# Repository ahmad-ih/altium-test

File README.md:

View this project on [CADLAB.io](https://cadlab.io/project/22601). 

# ANAVI Infrared pHAT

ANAVI Infrared pHAT is an open source hardware Raspberry Pi pHAT (add-on board) for rapid prototyping of Internet of Things (IoT) powered by free and open source software. It features:

* 2x IR transmitters
* IR receiver (IR photo sensor)
* Slots for up to 3 plug and play I2C sensors for temperature, barometric pressure, humidity and light
* UART (Universal asynchronous receiver/transmitter) pins for debugging

ANAVI Infrared pHAT is available at [CrowdSupply](https://www.crowdsupply.com/anavi-technology/infrared-phat).

# License

The project is released under the [Creative Commons Attribution-ShareAlike 4.0 International (CC BY-SA 4.0)](https://creativecommons.org/licenses/by-sa/4.0/).

Note: This is a human-readable summary of (and not a substitute for) the [license](https://creativecommons.org/licenses/by-sa/4.0/legalcode).

You are free to:

Share — copy and redistribute the material in any medium or format Adapt — remix, transform, and build upon the material for any purpose, even commercially. The licensor cannot revoke these freedoms as long as you follow the license terms. Under the following terms:

Attribution — You must give appropriate credit, provide a link to the license, and indicate if changes were made. You may do so in any reasonable manner, but not in any way that suggests the licensor endorses you or your use. ShareAlike — If you remix, transform, or build upon the material, you must distribute your contributions under the same license as the original. No additional restrictions — You may not apply legal terms or technological measures that legally restrict others from doing anything the license permits. Notices:

You do not have to comply with the license for elements of the material in the public domain or where your use is permitted by an applicable exception or limitation. No warranties are given. The license may not give you all of the permissions necessary for your intended use. For example, other rights such as publicity, privacy, or moral rights may limit how you use the material.

You will have to provide a link to the original creator of the project http://www.anavi.technology on any documentation or website.

Credit can be attributed through a link to the creator website: http://www.anavi.technology

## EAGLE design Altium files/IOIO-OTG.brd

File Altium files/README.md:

## NanoBoard-NB1

The NanoBoard-NB1 is Altium's legacy development platform for the rapid testing of FPGA designs. It consists of a motherboard with a variety of commonly used peripherals, and a range of plug-in FPGA or CPLD daughter boards.

The emergence of low-cost FPGA and CPLD devices from multiple vendors has resulted in the need
for a state of the art development system. The NB1 NanoBoard, in conjunction with the Altium
Designer PC-based development software allows hardware engineers and embedded systems
developers to develop and evaluate complex programmable logic-based systems.

In addition to providing schematic and PCB tools, the Altium Designer development system also allows
complete FPGA designs to be created, designed and debugged. FPGA projects can be created with
the schematic editor, using supplied schematic library components covering an extensive palette of IP
functions, including a range of industry-standard microcontrollers. 

The NanoBoard includes a unique communications protocol called NanoTalk, that provides connection
between a host PC running the software and the NanoBoard. NanoTalk provides the ability to
daisychain a number of NanoBoards, and communications access from the software to all resources
on the NanoBoard, or daisychained sequence of NanoBoards. 

Documentation
--------------
* **[Technical Reference for Altium's NanoBoard-NB1](http://valhalla.altium.com/Learning-Guides/Legacy/TR0102%20NanoBoard%20Technical%20Reference%20Manual%20-%20NB1.pdf)**
* **[Bootstrapping the Daughter Board FPGA on the NanoBoard-NB1](https://techdocs.altium.com/display/ADOH/Bootstrapping+the+Daughter+Board+FPGA+on+the+NanoBoard-NB1)**
* **[Utilizing the SPI Flash Memory on the NanoBoard-NB1](https://techdocs.altium.com/display/ADOH/Utilizing+the+SPI+Flash+Memory+on+the+NanoBoard-NB1)**
* **[Updating the Firmware on the NanoBoard-NB1](https://techdocs.altium.com/display/ADOH/Updating+the+Firmware+on+the+NanoBoard-NB1)**

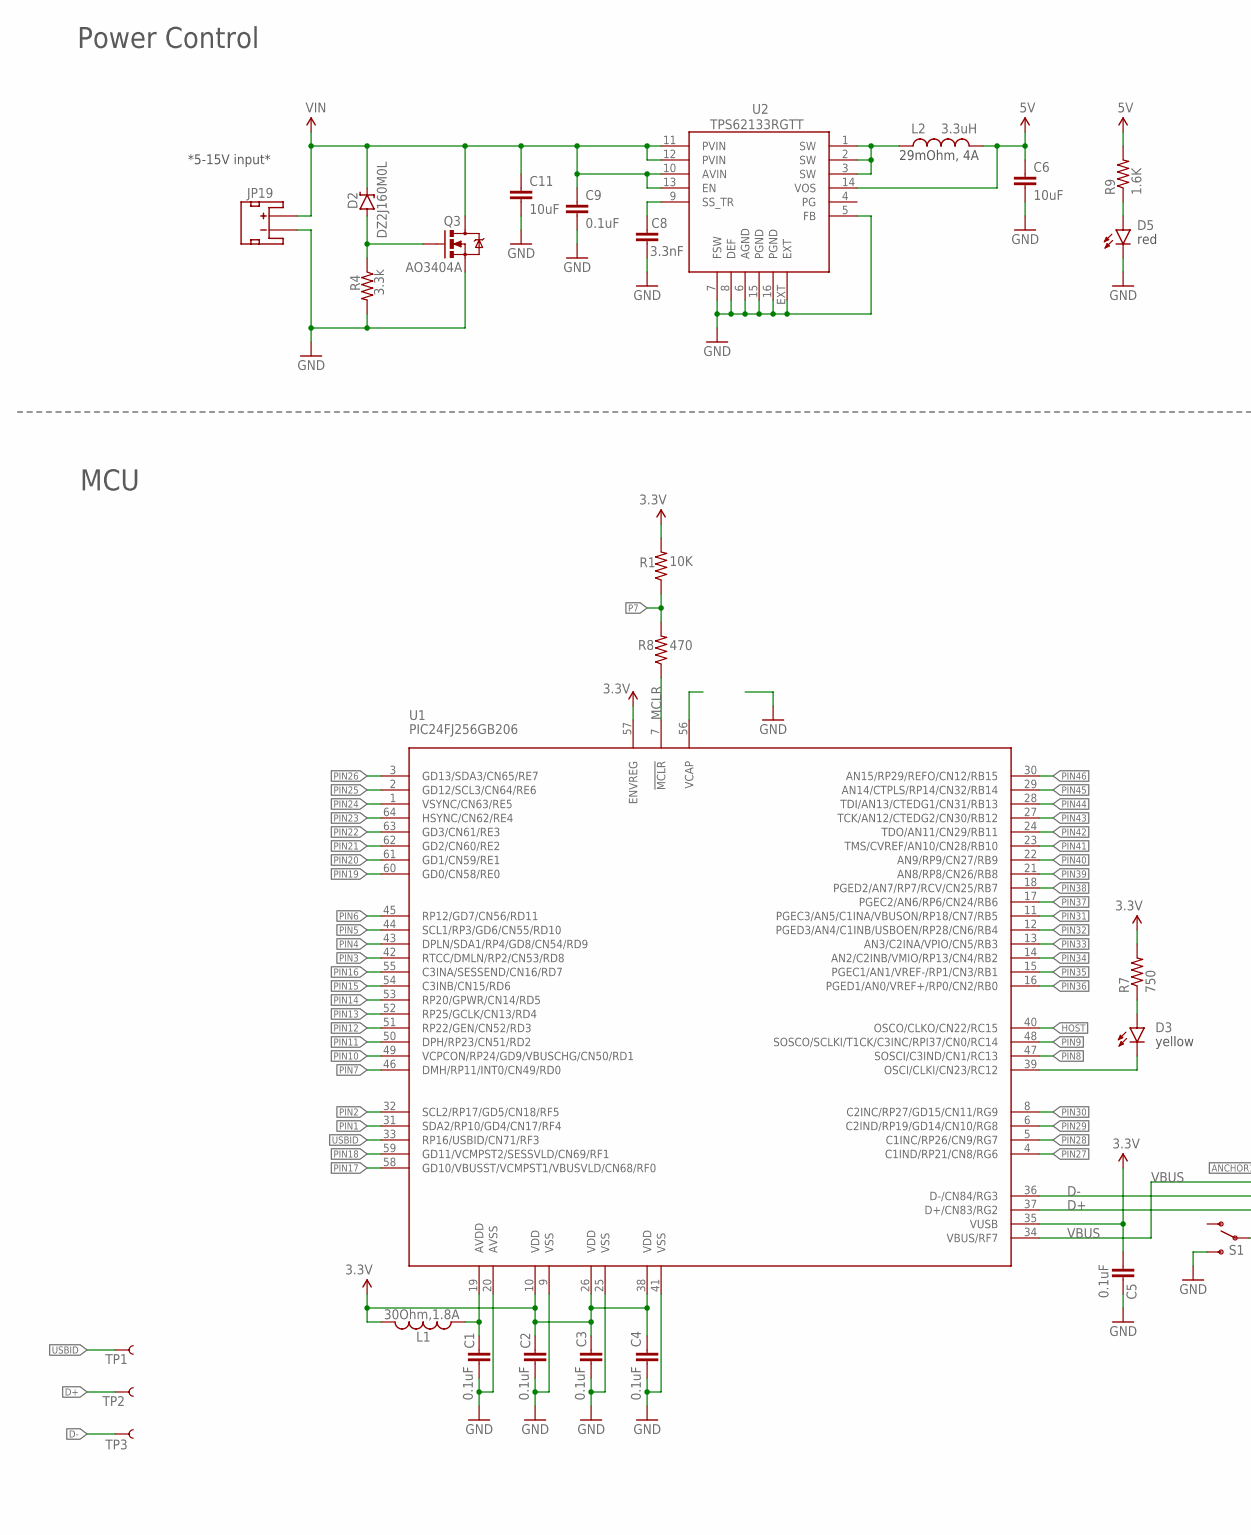
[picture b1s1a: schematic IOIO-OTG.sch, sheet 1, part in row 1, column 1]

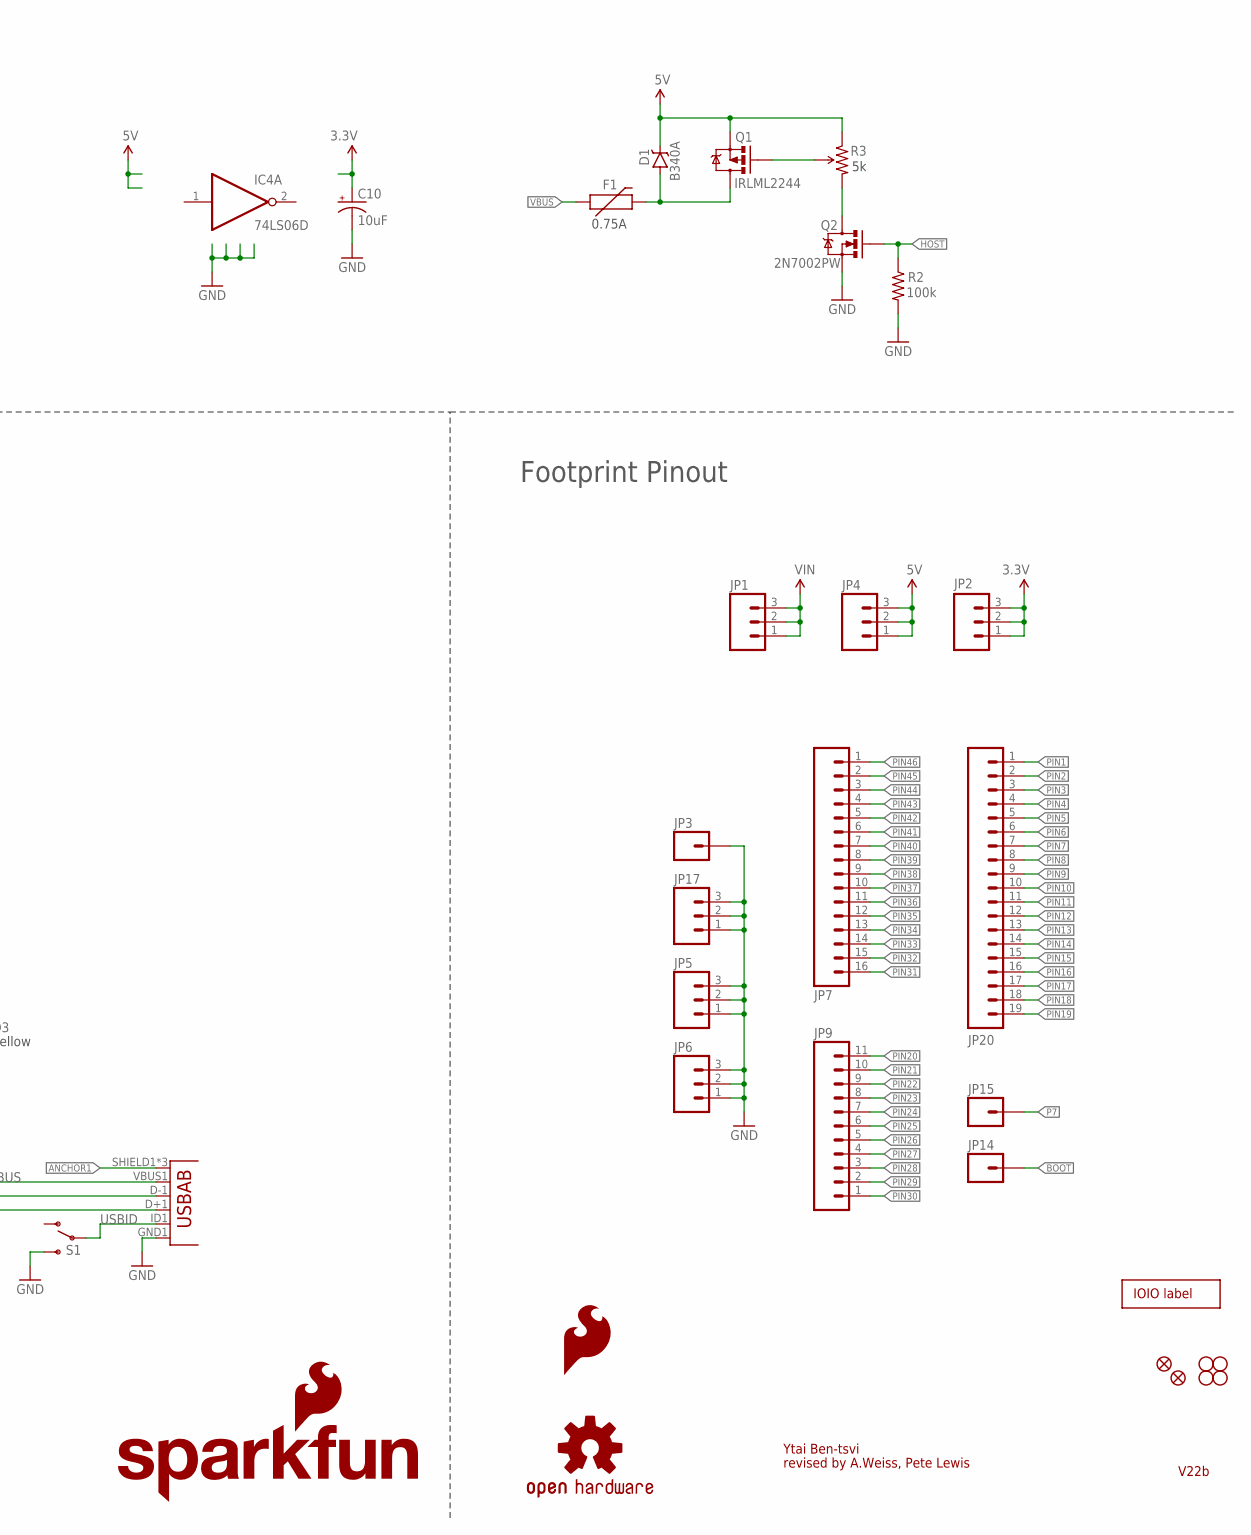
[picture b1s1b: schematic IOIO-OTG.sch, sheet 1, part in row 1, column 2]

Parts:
C1, C2, C3, C4, C5, C9: 0.1uF; 0603-CAP
C6: 10uF; 0805-CAP; PART# LMK212BJ106KG-T
C8: 3.3nF; 0603-CAP
C10: 10uF; EIA3216; PART# TAJA106K016RNJ
C11: 10uF; 1210; PART# UMK325C7106MM-T
D1: B340A; SMA-DIODE; PART# B340A
D2: DZ2J160M0L; PANASONIC_SMINI2-F5-B; PART# DZ2J150M0L
D3: Yellow; LED-0603
D5: Red; LED-0603
F1: 0.75A; PTC-1206; PART# 0ZCA0075FF2G
IC4: 74LS06D; SO14
JP1, JP2, JP4, JP5, JP6, JP17: M03PTH; 1X03
JP3, JP14, JP15: M01PTH; 1X01
JP7: M161X16_NO_SILK; 1X16_NO_SILK
JP8, JP16: FIDUCIALUFIDUCIAL; MICRO-FIDUCIAL
JP9: M111X11_NO_SILK; 1X11_NO_SILK
JP10, JP11, JP12, JP13: STAND-OFF
JP19: JST; JST-2-SMD
JP20: M191X19_NO_SILK; 1X19_NO_SILK
JP21: AB MICRO USB; USB-AB-MICRO-SMD_V03
L1: 30Ohm,1.8A; 0603
L2: VLC5045T-3R3N; CR54
LOGO1: OSHW-LOGOS; OSHW-LOGO-S
LOGO2: SFE_LOGO_NAME_FLAME.1_INCH; SFE_LOGO_NAME_FLAME_.1
LOGO3: SFE_LOGO_FLAME.1_INCH; SFE_LOGO_FLAME_.1
Q1: IRLML2244; SOT23-3
Q2: 2N7002PW; SOT323; PART# 2N7002PW
Q3: MOSFET-NCHANNELAO3404A; SOT23-3; PART# AO3404A
R1: 10K; 0603-RES
R2: 100k; 0603-RES
R3: TS53YL502MR10; TRIMPOT_5MM; PART# TS53YL502MR10
R4: 3.3k; 0603-RES
R7: 750; 0603-RES
R8: 470; 0603-RES
R9: 1.6K; 0603-RES
S1: SWITCH_SPDT; KPS-1290
TP1, TP2, TP3: TEST-POINT3; PAD.03X.03
U1: PIC24FJ256GB206; PIC24FXXX_TQFP64
U2: TPS62133RGTT; QFN16-3X3MM_1:1_V03
U$6: IOIO-OTG; IOIO-OTG-COPPER-EXPOSED

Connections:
3.3V: C2.1, C3.1, C4.1, C5.1, C10.A (+), JP2.1, JP2.2, JP2.3, L1.2, R1.2, R7.2, U1.10 (VDD), U1.26 (VDD), U1.35 (VUSB), U1.38 (VDD), U1.57 (ENVREG)
5V: C6.1, D1.C, JP4.1, JP4.2, JP4.3, L2.P$2 (2), Q1.2 (S), R3.A (CCW), R9.2, U2.14 (VOS)
ANCHOR1: JP21.SHIELD1 (SHIELD), JP21.SHIELD2 (SHIELD), JP21.SHIELD3 (SHIELD)
BOOT: D3.C, JP14.1, U1.39 (OSCI/CLKI/CN23/RC12)
D+: JP21.D+1 (D+), TP2.P$1, U1.37 (D+/CN83/RG2)
D-: JP21.D-1 (D-), TP3.P$1, U1.36 (D-/CN84/RG3)
GND: C1.2, C2.2, C3.2, C4.2, C5.2, C6.2, C8.2, C9.2, C10.C (-), C11.2, D5.C, IC4.7 (GND), JP3.1, JP5.1, JP5.2, JP5.3, JP6.1, JP6.2, JP6.3, JP17.1, JP17.2, JP17.3, JP19.1 (-), JP21.GND1 (GND), Q2.2 (S), Q3.2 (S), R2.2, R4.2, S1.S, U1.9 (VSS), U1.20 (AVSS), U1.25 (VSS), U1.41 (VSS), U2.5 (FB), U2.6 (AGND), U2.7 (FSW), U2.8 (DEF), U2.15 (PGND), U2.16 (PGND), U2.EXT; also elsewhere on the board
HOST: Q2.1 (G), R2.1, U1.40 (OSCO/CLKO/CN22/RC15)
MCLR: R8.1, U1.7 (!MCLR)
unnamed: Q1.1 (G), R3.B (WIPER)
unnamed: D3.A, R7.1
unnamed: D5.A, R9.1
unnamed: D1.A, F1.2, Q1.3 (D)
unnamed: L2.P$1 (1), U2.1 (SW), U2.2 (SW), U2.3 (SW)
unnamed: C8.1, U2.9 (SS_TR)
unnamed: Q2.3 (D), R3.C (CW)
unnamed: C1.1, L1.1, U1.19 (AVDD)
unnamed: D2.A, Q3.1 (G), R4.1
P7: JP15.1, R1.1, R8.2
PIN1: JP20.1, U1.31 (SDA2/RP10/GD4/CN17/RF4)
PIN2: JP20.2, U1.32 (SCL2/RP17/GD5/CN18/RF5)
PIN3: JP20.3, U1.42 (RTCC/DMLN/RP2/CN53/RD8)
PIN4: JP20.4, U1.43 (DPLN/SDA1/RP4/GD8/CN54/RD9)
PIN5: JP20.5, U1.44 (SCL1/RP3/GD6/CN55/RD10)
PIN6: JP20.6, U1.45 (RP12/GD7/CN56/RD11)
PIN7: JP20.7, U1.46 (DMH/RP11/INT0/CN49/RD0)
PIN8: JP20.8, U1.47 (SOSCI/C3IND/CN1/RC13)
PIN9: JP20.9, U1.48 (SOSCO/SCLKI/T1CK/C3INC/RPI37/CN0/RC14)
PIN10: JP20.10, U1.49 (VCPCON/RP24/GD9/VBUSCHG/CN50/RD1)
PIN11: JP20.11, U1.50 (DPH/RP23/CN51/RD2)
PIN12: JP20.12, U1.51 (RP22/GEN/CN52/RD3)
PIN13: JP20.13, U1.52 (RP25/GCLK/CN13/RD4)
PIN14: JP20.14, U1.53 (RP20/GPWR/CN14/RD5)
PIN15: JP20.15, U1.54 (C3INB/CN15/RD6)
PIN16: JP20.16, U1.55 (C3INA/SESSEND/CN16/RD7)
PIN17: JP20.17, U1.58 (GD10/VBUSST/VCMPST1/VBUSVLD/CN68/RF0)
PIN18: JP20.18, U1.59 (GD11/VCMPST2/SESSVLD/CN69/RF1)
PIN19: JP20.19, U1.60 (GD0/CN58/RE0)
PIN20: JP9.11, U1.61 (GD1/CN59/RE1)
PIN21: JP9.10, U1.62 (GD2/CN60/RE2)
PIN22: JP9.9, U1.63 (GD3/CN61/RE3)
PIN23: JP9.8, U1.64 (HSYNC/CN62/RE4)
PIN24: JP9.7, U1.1 (VSYNC/CN63/RE5)
PIN25: JP9.6, U1.2 (GD12/SCL3/CN64/RE6)
PIN26: JP9.5, U1.3 (GD13/SDA3/CN65/RE7)
PIN27: JP9.4, U1.4 (C1IND/RP21/CN8/RG6)
PIN28: JP9.3, U1.5 (C1INC/RP26/CN9/RG7)
PIN29: JP9.2, U1.6 (C2IND/RP19/GD14/CN10/RG8)
PIN30: JP9.1, U1.8 (C2INC/RP27/GD15/CN11/RG9)
PIN31: JP7.16, U1.11 (PGEC3/AN5/C1INA/VBUSON/RP18/CN7/RB5)
PIN32: JP7.15, U1.12 (PGED3/AN4/C1INB/USBOEN/RP28/CN6/RB4)
PIN33: JP7.14, U1.13 (AN3/C2INA/VPIO/CN5/RB3)
PIN34: JP7.13, U1.14 (AN2/C2INB/VMIO/RP13/CN4/RB2)
PIN35: JP7.12, U1.15 (PGEC1/AN1/VREF-/RP1/CN3/RB1)
PIN36: JP7.11, U1.16 (PGED1/AN0/VREF+/RP0/CN2/RB0)
PIN37: JP7.10, U1.17 (PGEC2/AN6/RP6/CN24/RB6)
PIN38: JP7.9, U1.18 (PGED2/AN7/RP7/RCV/CN25/RB7)
PIN39: JP7.8, U1.21 (AN8/RP8/CN26/RB8)
PIN40: JP7.7, U1.22 (AN9/RP9/CN27/RB9)
PIN41: JP7.6, U1.23 (TMS/CVREF/AN10/CN28/RB10)
PIN42: JP7.5, U1.24 (TDO/AN11/CN29/RB11)
PIN43: JP7.4, U1.27 (TCK/AN12/CTEDG2/CN30/RB12)
PIN44: JP7.3, U1.28 (TDI/AN13/CTEDG1/CN31/RB13)
PIN45: JP7.2, U1.29 (AN14/CTPLS/RP14/CN32/RB14)
PIN46: JP7.1, U1.30 (AN15/RP29/REFO/CN12/RB15)
USBID: JP21.ID1 (USBID), S1.P, TP1.P$1, U1.33 (RP16/USBID/CN71/RF3)
VBUS: F1.1, JP21.VBUS1 (VBUS), U1.34 (VBUS/RF7)
VCC: IC4.14 (VCC); also elsewhere on the board
VIN: C9.1, C11.1, D2.C, JP1.1, JP1.2, JP1.3, JP19.2 (+), Q3.3 (D), U2.10 (AVIN), U2.11 (PVIN), U2.12 (PVIN), U2.13 (EN)

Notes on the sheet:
Ytai Ben-tsvi
revised by A.Weiss, Pete Lewis
*5-15V input*
yellow
red
0.75A
29mOhm, 4A
Footprint Pinout
Power Control
MCU
V22b
DZ2J160M0L
AO3404A
2N7002PW
IRLML2244
B340A

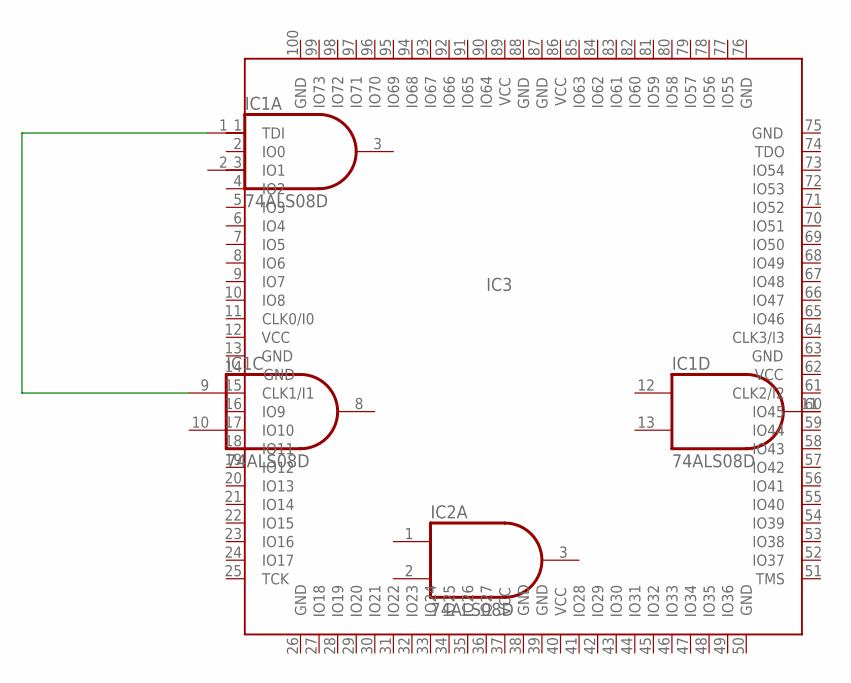
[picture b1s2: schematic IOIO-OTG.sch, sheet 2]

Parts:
IC1, IC2: 74ALS08D; SO14
IC3: M5-75P100; PQFP100

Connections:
GND: IC1.7 (GND), IC2.7 (GND), IC3.13 (GND), IC3.14 (GND), IC3.26 (GND), IC3.38 (GND), IC3.39 (GND), IC3.50 (GND), IC3.63 (GND), IC3.75 (GND), IC3.76 (GND), IC3.87 (GND), IC3.88 (GND), IC3.100 (GND); also elsewhere on the board
unnamed: IC1.1 (I0), IC1.9 (I0)
unnamed: IC1.11 (O), IC3.60 (IO45)
VCC: IC1.14 (VCC), IC2.14 (VCC), IC3.12 (VCC), IC3.37 (VCC), IC3.40 (VCC), IC3.62 (VCC), IC3.86 (VCC), IC3.89 (VCC); also elsewhere on the board

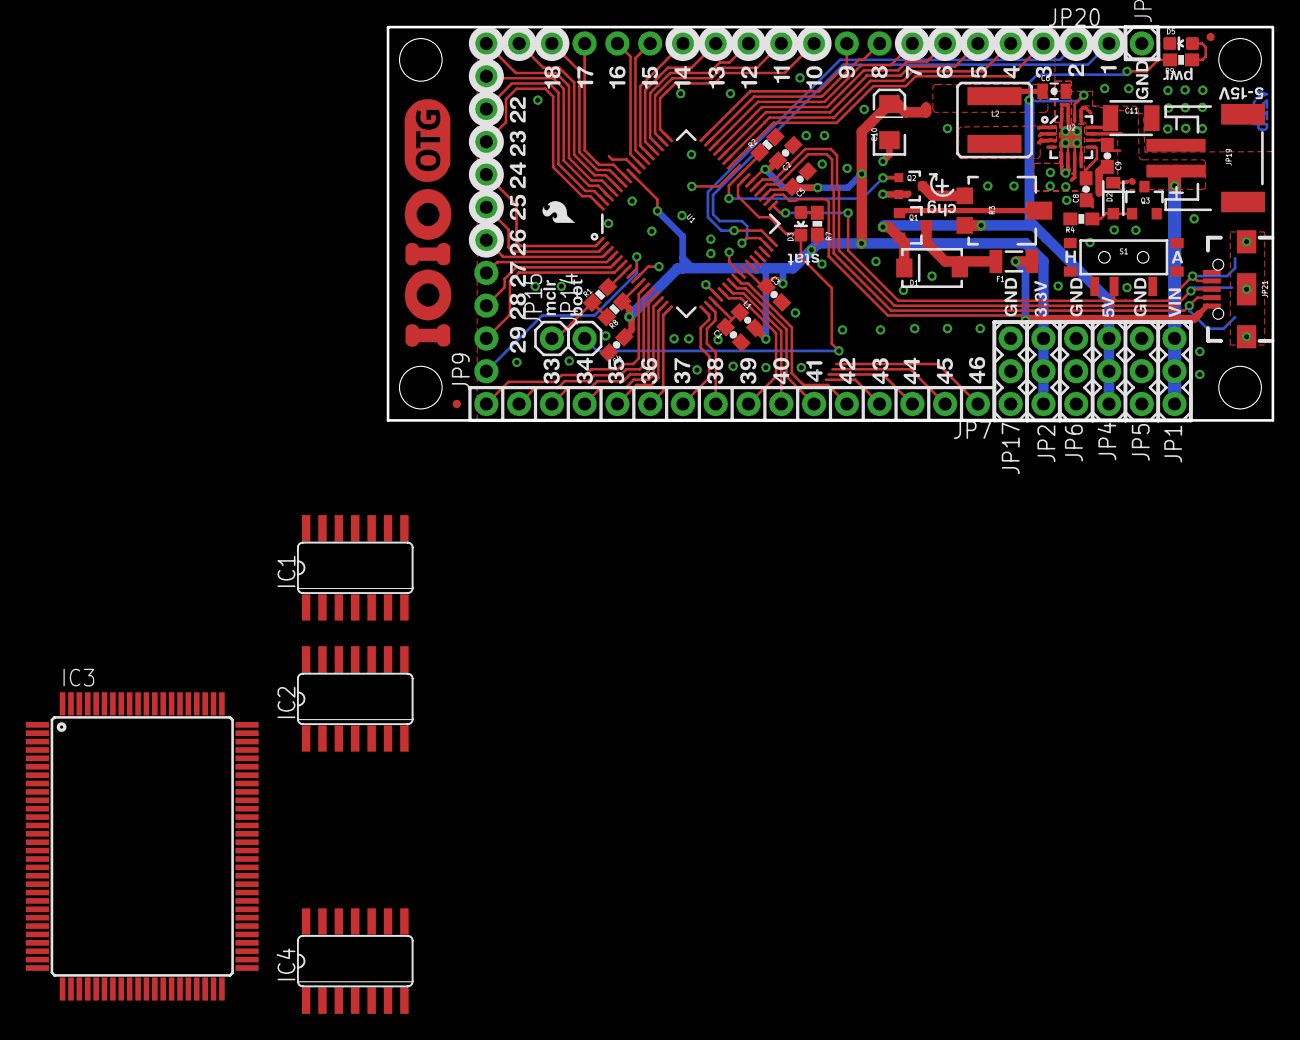
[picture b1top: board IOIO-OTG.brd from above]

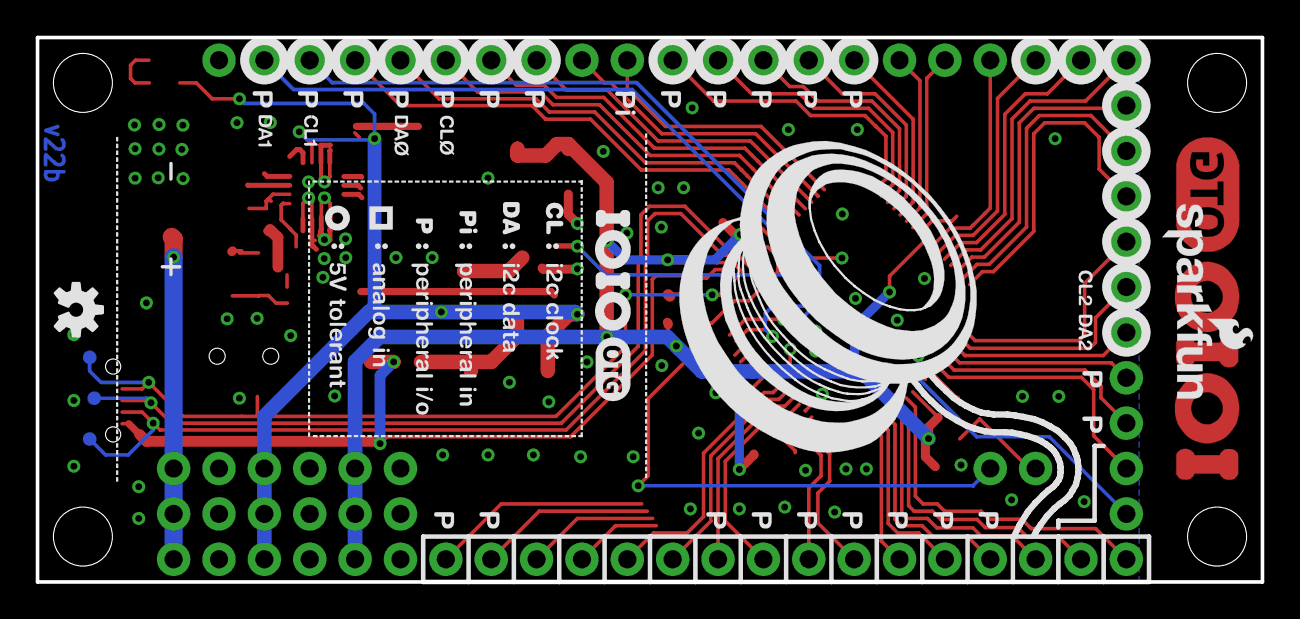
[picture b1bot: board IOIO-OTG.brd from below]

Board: 2 copper layers, 68.6 x 30.5 mm, 61 parts (5 on the bottom side), 71 nets.

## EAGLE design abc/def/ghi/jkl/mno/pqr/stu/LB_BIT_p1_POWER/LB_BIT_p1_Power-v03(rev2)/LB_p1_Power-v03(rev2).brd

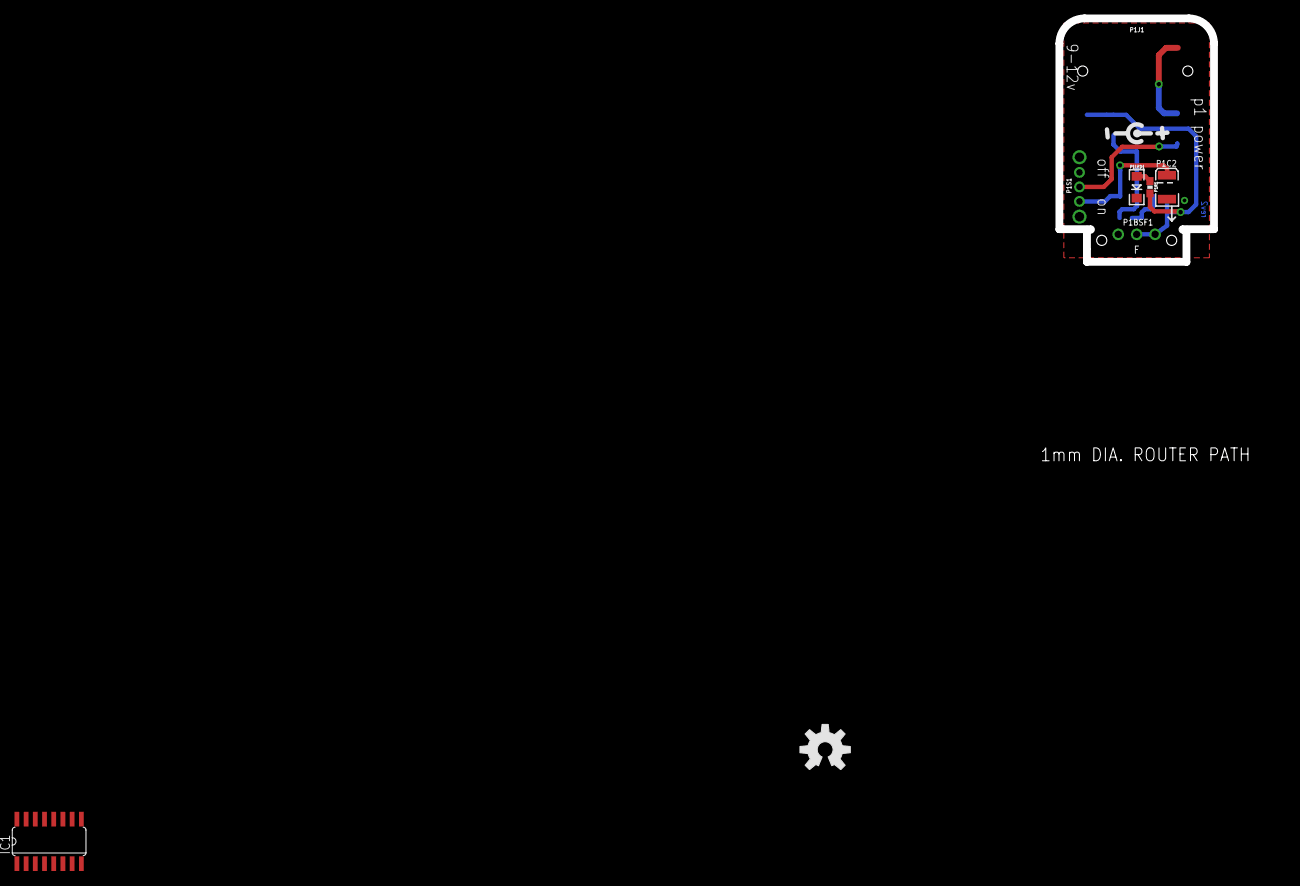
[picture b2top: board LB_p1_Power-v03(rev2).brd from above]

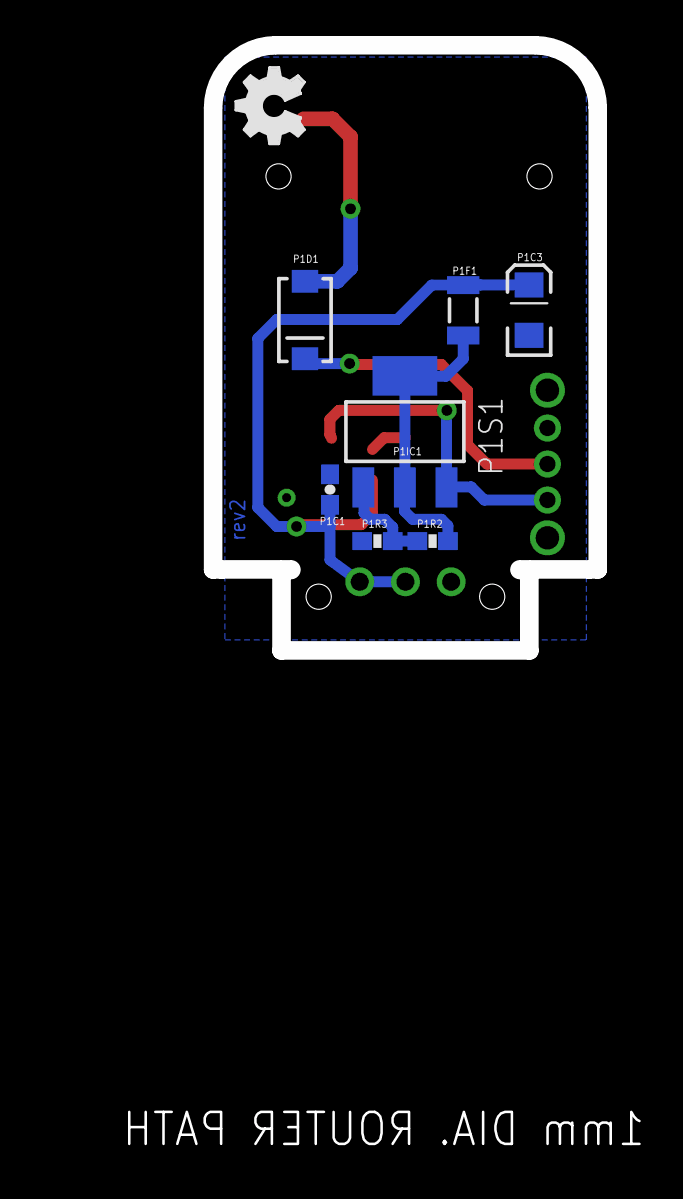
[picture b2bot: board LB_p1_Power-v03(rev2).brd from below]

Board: 2 copper layers, 21.4 x 33.6 mm, 19 parts (8 on the bottom side), 7 nets.

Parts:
IC1: 4500D; SO16
P1BSF1: BITSNAP_V03_FEMALE
P1C1: 0.1uF; 0603-CAP
P1C2: 10uF/20V; EIA3528
P1C3: 10uF; EIA3216
P1D1: MBRA140; SMA-DIODE
P1F1: 500mA PTC; PTC-1206
P1IC1: LM1117; SOT223
P1LED1: RED; LED-1206
P1R1: 330; 0603-RES
P1R2: 240; 0603-RES
P1R3: 720; 0603-RES
P1S1: SWITCH-SPDT; LITTLEBITS_SWITCH-DICGU_SPDT
U$1: +/-PWR_JACK
U$2: OSHW_FILLX150_NOTEXT
U$3: OSHW-LOGOL; OSHW-LOGO-L
U$4: LB_CREDITS; OSHWCREDIT
U$5: FRAME-LETTER-OHWOHW; FABDWG01-OHW
U$12: LB_PWR_LEGS

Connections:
GND: P1BSF1.GND, P1C1.2, P1C2.C, P1C3.C, P1LED1.C, P1R3.1
unnamed: P1D1.C, P1S1.COM
unnamed: P1F1.1, P1IC1.2, P1IC1.4, P1R2.2
unnamed: P1IC1.1, P1R2.1, P1R3.2
unnamed: P1C2.A, P1IC1.3, P1S1.2
unnamed: P1LED1.A, P1R1.1
VCC: P1BSF1.SIG, P1BSF1.VCC, P1C1.1, P1C3.A, P1F1.2, P1R1.2

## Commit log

2021-06-10 1st commit
2021-06-10 In branch br/%25
2021-06-10 in br/%&
2021-06-10 in br/#br%
2021-06-10 new files
2021-06-18 kicad files

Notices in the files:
parts and their libraries:
SparkFun-PowerIC: Licensing: CC v3.0 Share-Alike You are welcome to use this library for commercial purposes.
SparkFun-Resistors: Licensing: Creative Commons ShareAlike 4.0 International - https://creativecommons.org/licenses/by-sa/4.0
